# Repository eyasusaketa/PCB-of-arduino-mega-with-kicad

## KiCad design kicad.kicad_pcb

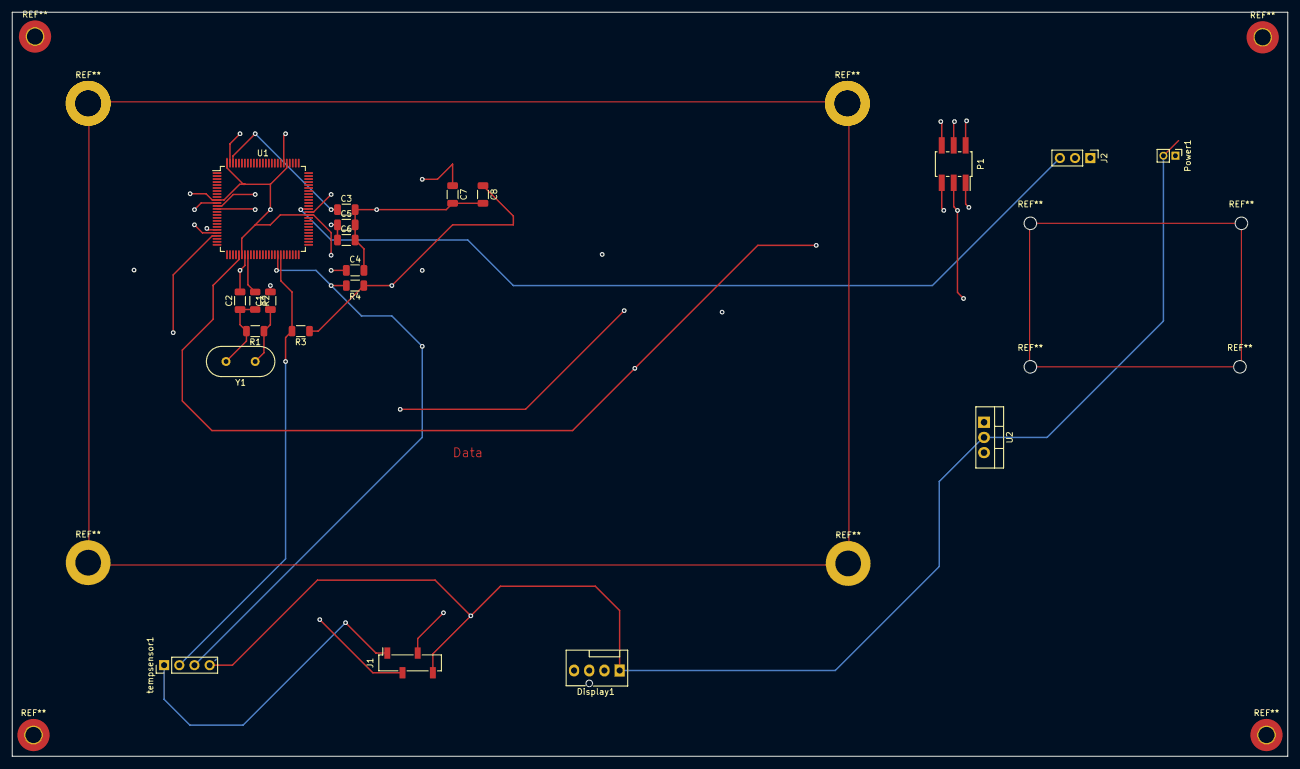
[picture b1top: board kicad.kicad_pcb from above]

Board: 4 copper layers, 213.4 x 124.5 mm, 21 parts (0 on the bottom side), 17 nets.

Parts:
C1, C2: 22pF; C_1206_3216Metric
C3: 100nF; C_1206_3216Metric
C4, C5, C6: 100n; C_1206_3216Metric
C7: 10uf; C_1206_3216Metric
C8: 1uf; C_1206_3216Metric
Display1: Nextion_Display; FanPinHeader_1x04_P2.54mm_Vertical
J1: HEART_BEAT SENSOR; PinSocket_1x04_P2.54mm_Vertical_SMD_Pin1Right
J2: Conn_01x03_Female; PinHeader_1x03_P2.54mm_Vertical
P1: SPI; PinSocket_2x03_P2.00mm_Vertical_SMD
Power1: POWER; PinHeader_1x02_P2.00mm_Vertical
R1: 1M; R_1206_3216Metric
R2: R; R_1206_3216Metric
R3, R4: 10k; R_1206_3216Metric
U1: ATmega2560-16A; TQFP-100_14x14mm_P0.5mm
U2: LM7805_TO220; TO-220-3_Vertical
Y1: 16MHz; Crystal_HC49-4H_Vertical
tempsensor1: temp.Sensor; PinHeader_1x04_P2.54mm_Vertical

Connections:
/+V: C7.1, Power1.1, U2.1 (VI)
/-V: C1.2, C2.2, C3.2, C4.2, C5.2, C6.2, C7.2, C8.2, Display1.1, J1.4, J2.1, P1.6, Power1.2, U1.11 (GND), U1.32 (GND), U1.62 (GND), U1.81 (GND), U1.99 (GND), U2.2 (GND), tempsensor1.4
/MISO: P1.1, U1.22 (PB3)
/MOSI: P1.4, U1.21 (PB2)
/RESET: P1.5, U1.30 (~RESET)
/RX: Display1.3, U1.12 (PH0)
/RX3: J2.3, U1.63 (PJ0)
/SCK: P1.3, U1.20 (PB1)
/SCL: J1.3, R4.2, U1.43 (PD0), tempsensor1.3
/SDA: J1.2, R3.2, U1.44 (PD1), tempsensor1.2
/TX: Display1.2, U1.13 (PH1)
/VCC: C8.1, Display1.4, J1.1, J2.2, P1.2, R3.1, R4.1, U1.10 (VCC), U1.31 (VCC), U1.61 (VCC), U1.80 (VCC), U1.100 (AVCC), U2.3 (VO), tempsensor1.1
unnamed: C1.1, R1.1, Y1.1
unnamed: C2.1, R1.2, R2.2, Y1.2
unnamed: C3.1, U1.98 (AREF)
unnamed: C4.1, C5.1, C6.1
unnamed: R2.1, U1.33 (XTAL2)
